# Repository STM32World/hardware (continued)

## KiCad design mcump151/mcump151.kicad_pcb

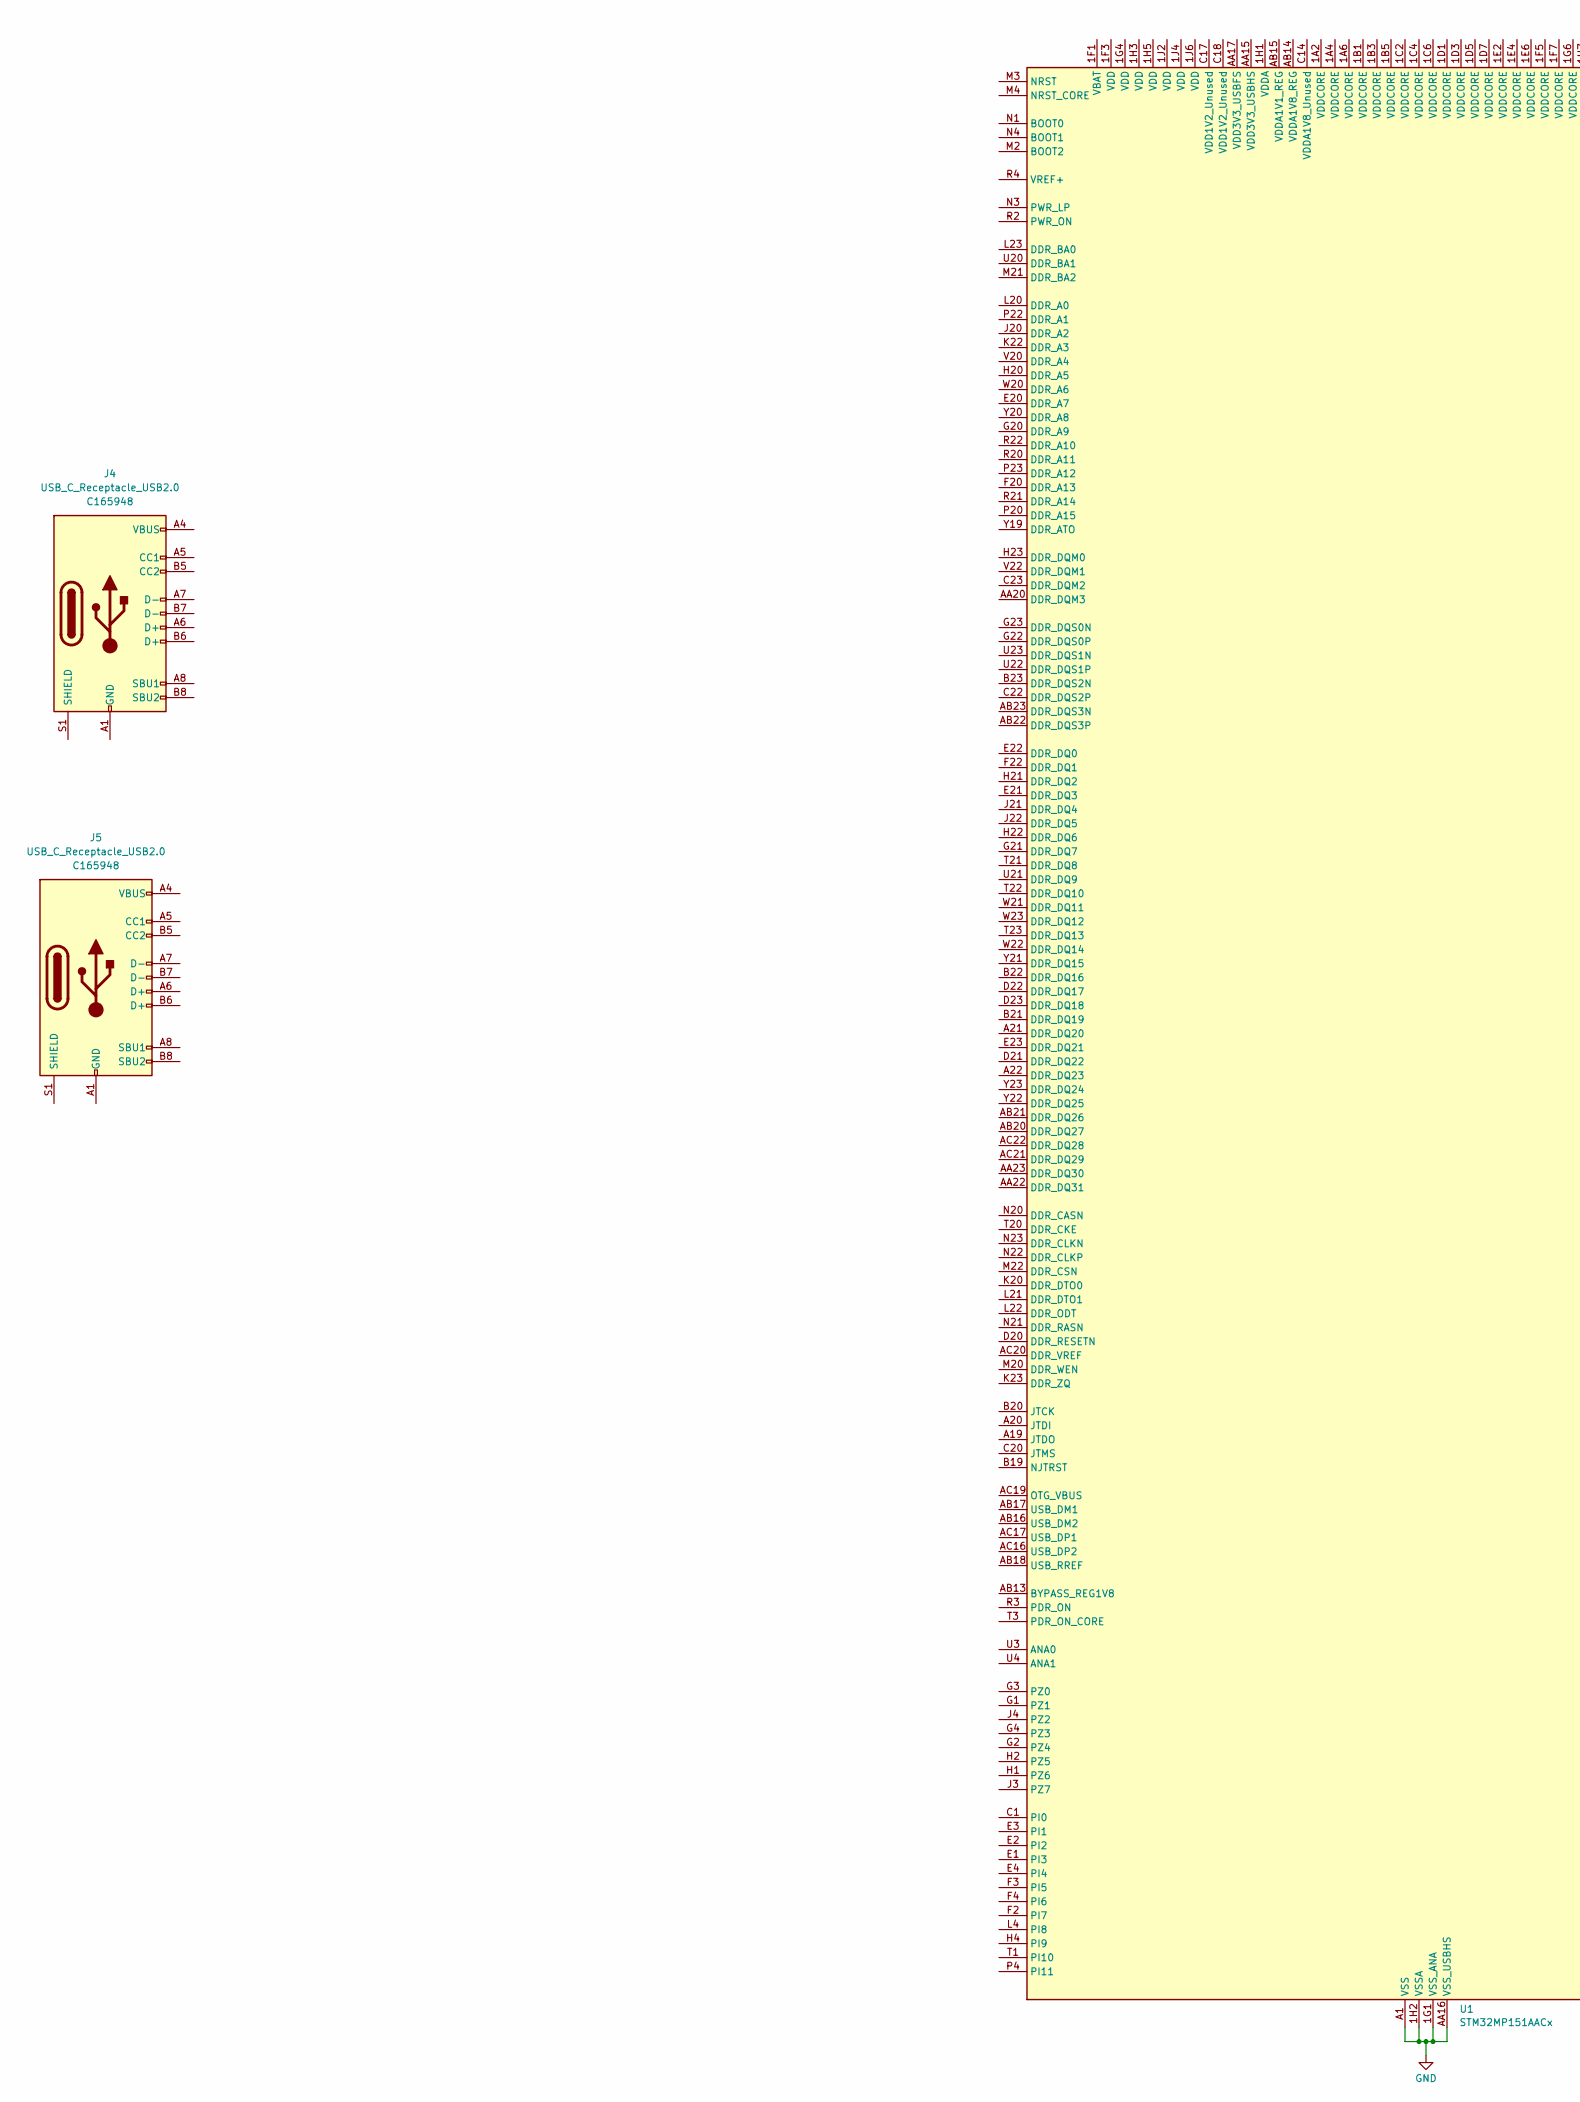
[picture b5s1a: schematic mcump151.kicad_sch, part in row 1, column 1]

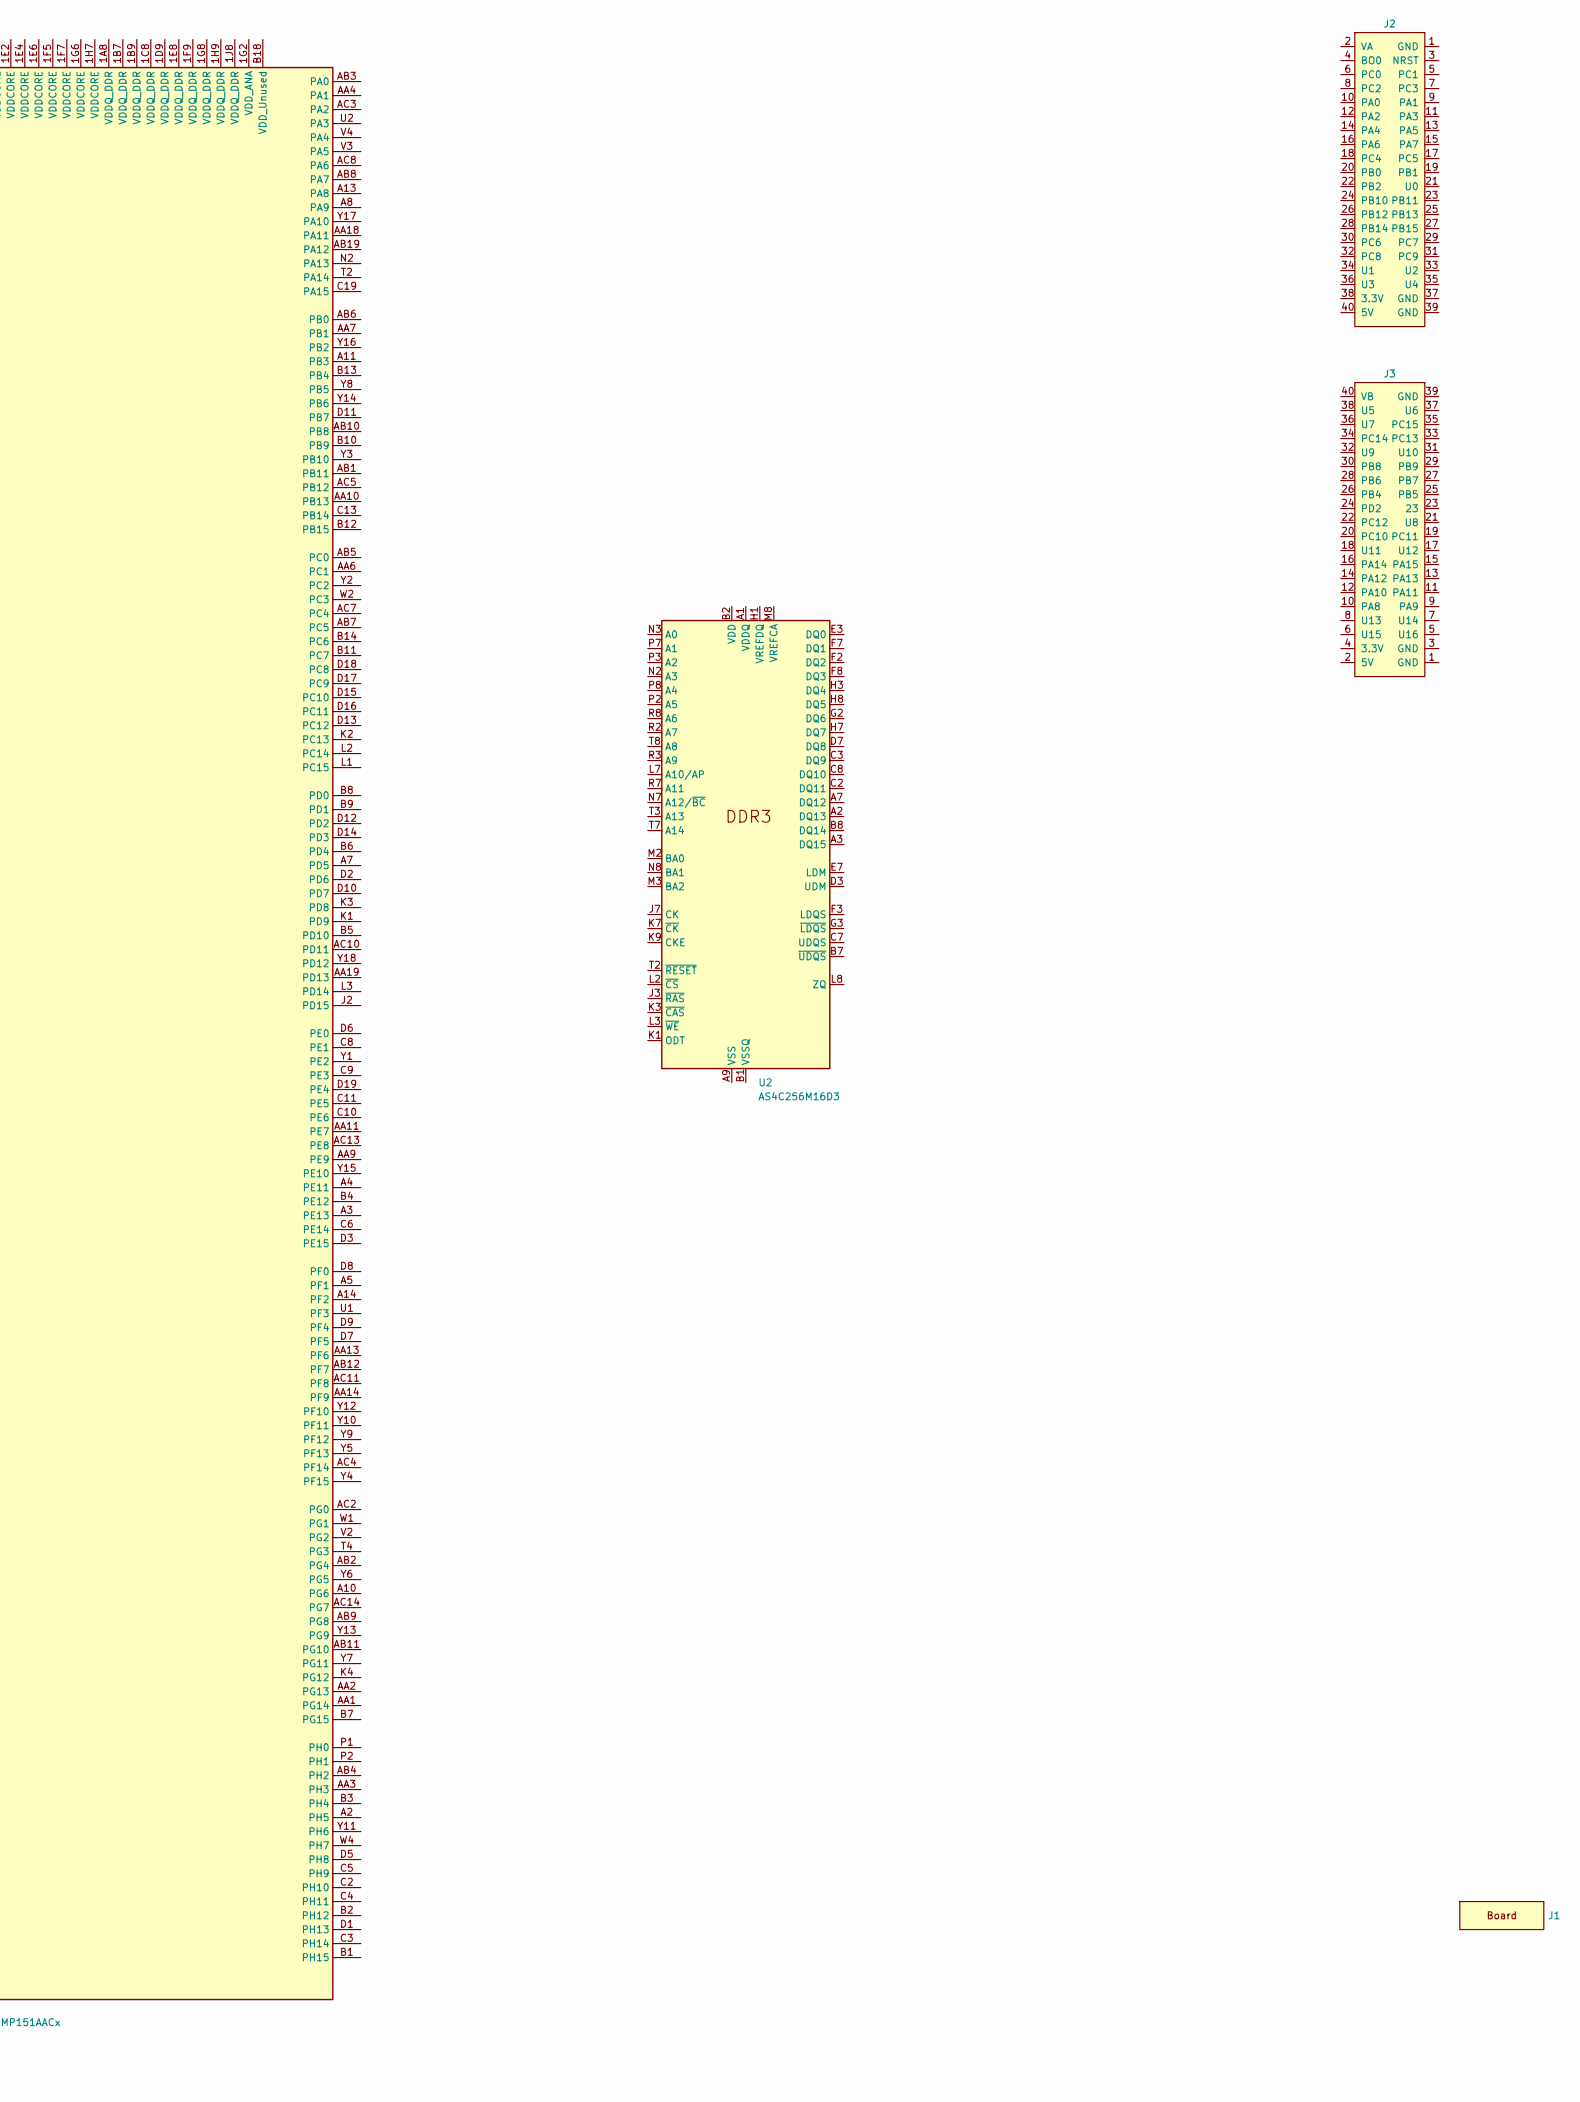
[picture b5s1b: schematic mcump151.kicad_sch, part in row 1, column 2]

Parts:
J1: STM32WORLD_BOARD
J2: STM32WORLD_CONNECTOR_1; PinSocket_2x20_P2.54mm_Vertical_Stackable; LCSC C35165
J3: STM32WORLD_CONNECTOR_2; PinSocket_2x20_P2.54mm_Vertical_Stackable; LCSC C35165
J4, J5: USB_C_Receptacle_USB2.0; USB_C_Receptacle_HRO_TYPE-C-31-M-12; LCSC C165948
U1: STM32MP151AACx; ST_TFBGA-361_12x12mm_Layout23x23_P0.5mmP0.65mm; LCSC C1555473
U2: AS4C256M16D3; BGA-96_9.0x13.0mm_Layout2x3x16_P0.8mm

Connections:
GND: U1.1A3 (VSS), U1.1A5 (VSS), U1.1A7 (VSS), U1.1B2 (VSS), U1.1B4 (VSS), U1.1B6 (VSS), U1.1B8 (VSS), U1.1C1 (VSS), U1.1C3 (VSS), U1.1C5 (VSS), U1.1C7 (VSS), U1.1C9 (VSS), U1.1D2 (VSS), U1.1D4 (VSS), U1.1D6 (VSS), U1.1D8 (VSS), U1.1E1 (VSS), U1.1E3 (VSS), U1.1E5 (VSS), U1.1E7 (VSS), U1.1E9 (VSS), U1.1F2 (VSS), U1.1F4 (VSS), U1.1F6 (VSS), U1.1F8 (VSS), U1.1G1 (VSS_ANA), U1.1G3 (VSS), U1.1G5 (VSS), U1.1G7 (VSS), U1.1G9 (VSS), U1.1H2 (VSSA), U1.1H4 (VSS), U1.1H6 (VSS), U1.1H8 (VSS), U1.1J3 (VSS), U1.1J5 (VSS), U1.1J7 (VSS), U1.A1 (VSS), U1.A23 (VSS), U1.AA5 (VSS), U1.AA8 (VSS), U1.AA12 (VSS), U1.AA16 (VSS_USBHS), U1.AA21 (VSS), U1.AC1 (VSS), U1.AC23 (VSS), U1.C7 (VSS), U1.C12 (VSS), U1.C16 (VSS), U1.C21 (VSS), U1.D4 (VSS), U1.F21 (VSS), U1.H3 (VSS), U1.K21 (VSS), U1.P3 (VSS), U1.P21 (VSS), U1.V21 (VSS), U1.W3 (VSS)
unnamed: J4.A1 (GND), J4.A12 (GND), J4.B1 (GND), J4.B12 (GND)
unnamed: J4.A4 (VBUS), J4.A9 (VBUS), J4.B4 (VBUS), J4.B9 (VBUS)
unnamed: J5.A1 (GND), J5.A12 (GND), J5.B1 (GND), J5.B12 (GND)
unnamed: J5.A4 (VBUS), J5.A9 (VBUS), J5.B4 (VBUS), J5.B9 (VBUS)
unnamed: U2.B2 (VDD), U2.D9 (VDD), U2.G7 (VDD), U2.K2 (VDD), U2.K8 (VDD), U2.N1 (VDD), U2.N9 (VDD), U2.R1 (VDD), U2.R9 (VDD)
unnamed: U2.A1 (VDDQ), U2.A8 (VDDQ), U2.C1 (VDDQ), U2.C9 (VDDQ), U2.D2 (VDDQ), U2.E9 (VDDQ), U2.F1 (VDDQ), U2.H2 (VDDQ), U2.H9 (VDDQ)
unnamed: U2.A9 (VSS), U2.B3 (VSS), U2.E1 (VSS), U2.G8 (VSS), U2.J2 (VSS), U2.J8 (VSS), U2.M1 (VSS), U2.M9 (VSS), U2.P1 (VSS), U2.P9 (VSS), U2.T1 (VSS), U2.T9 (VSS)
unnamed: U2.B1 (VSSQ), U2.B9 (VSSQ), U2.D1 (VSSQ), U2.D8 (VSSQ), U2.E2 (VSSQ), U2.E8 (VSSQ), U2.F9 (VSSQ), U2.G1 (VSSQ), U2.G9 (VSSQ)

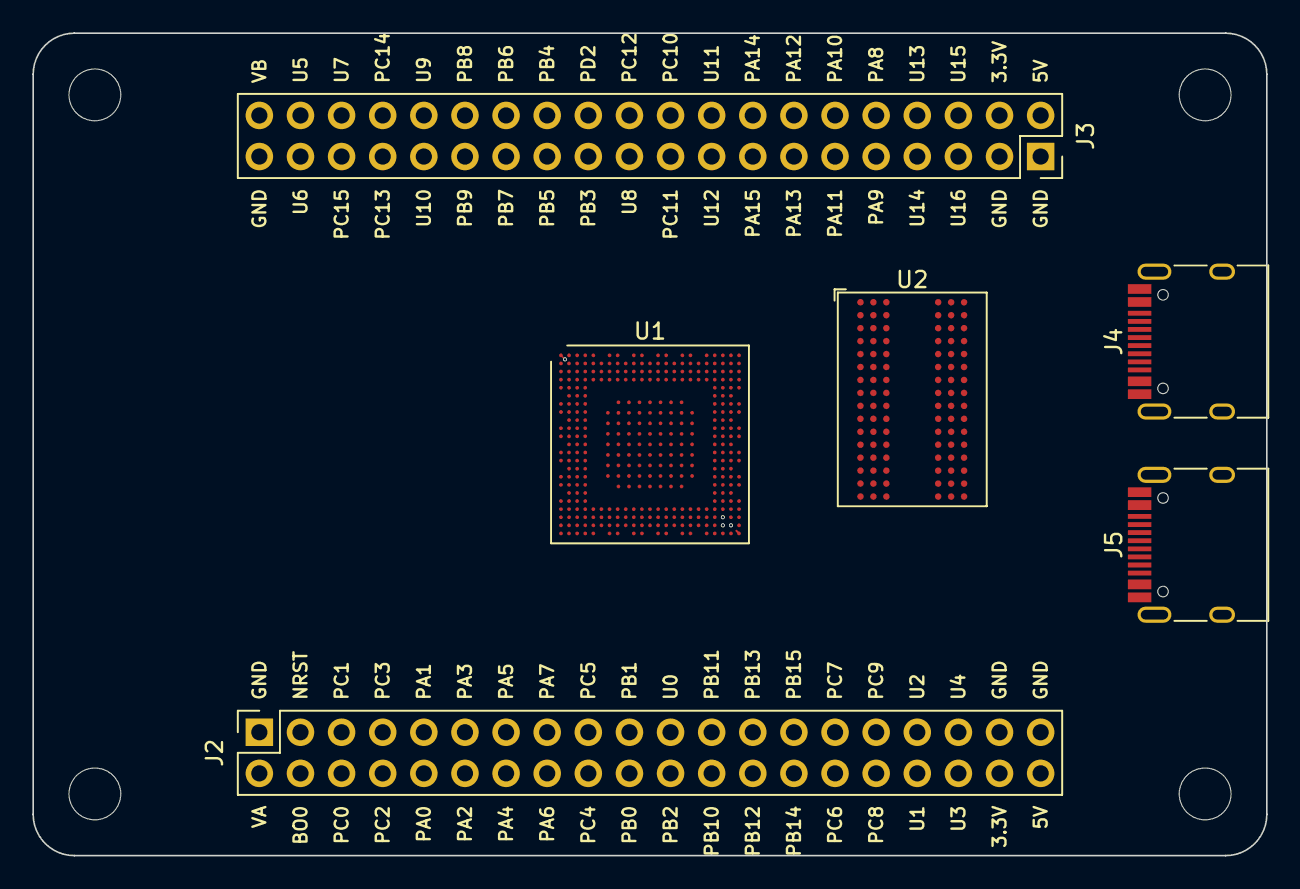
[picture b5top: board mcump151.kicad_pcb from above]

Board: 8 copper layers, 76.2 x 50.8 mm, 7 parts (0 on the bottom side), 9 nets.

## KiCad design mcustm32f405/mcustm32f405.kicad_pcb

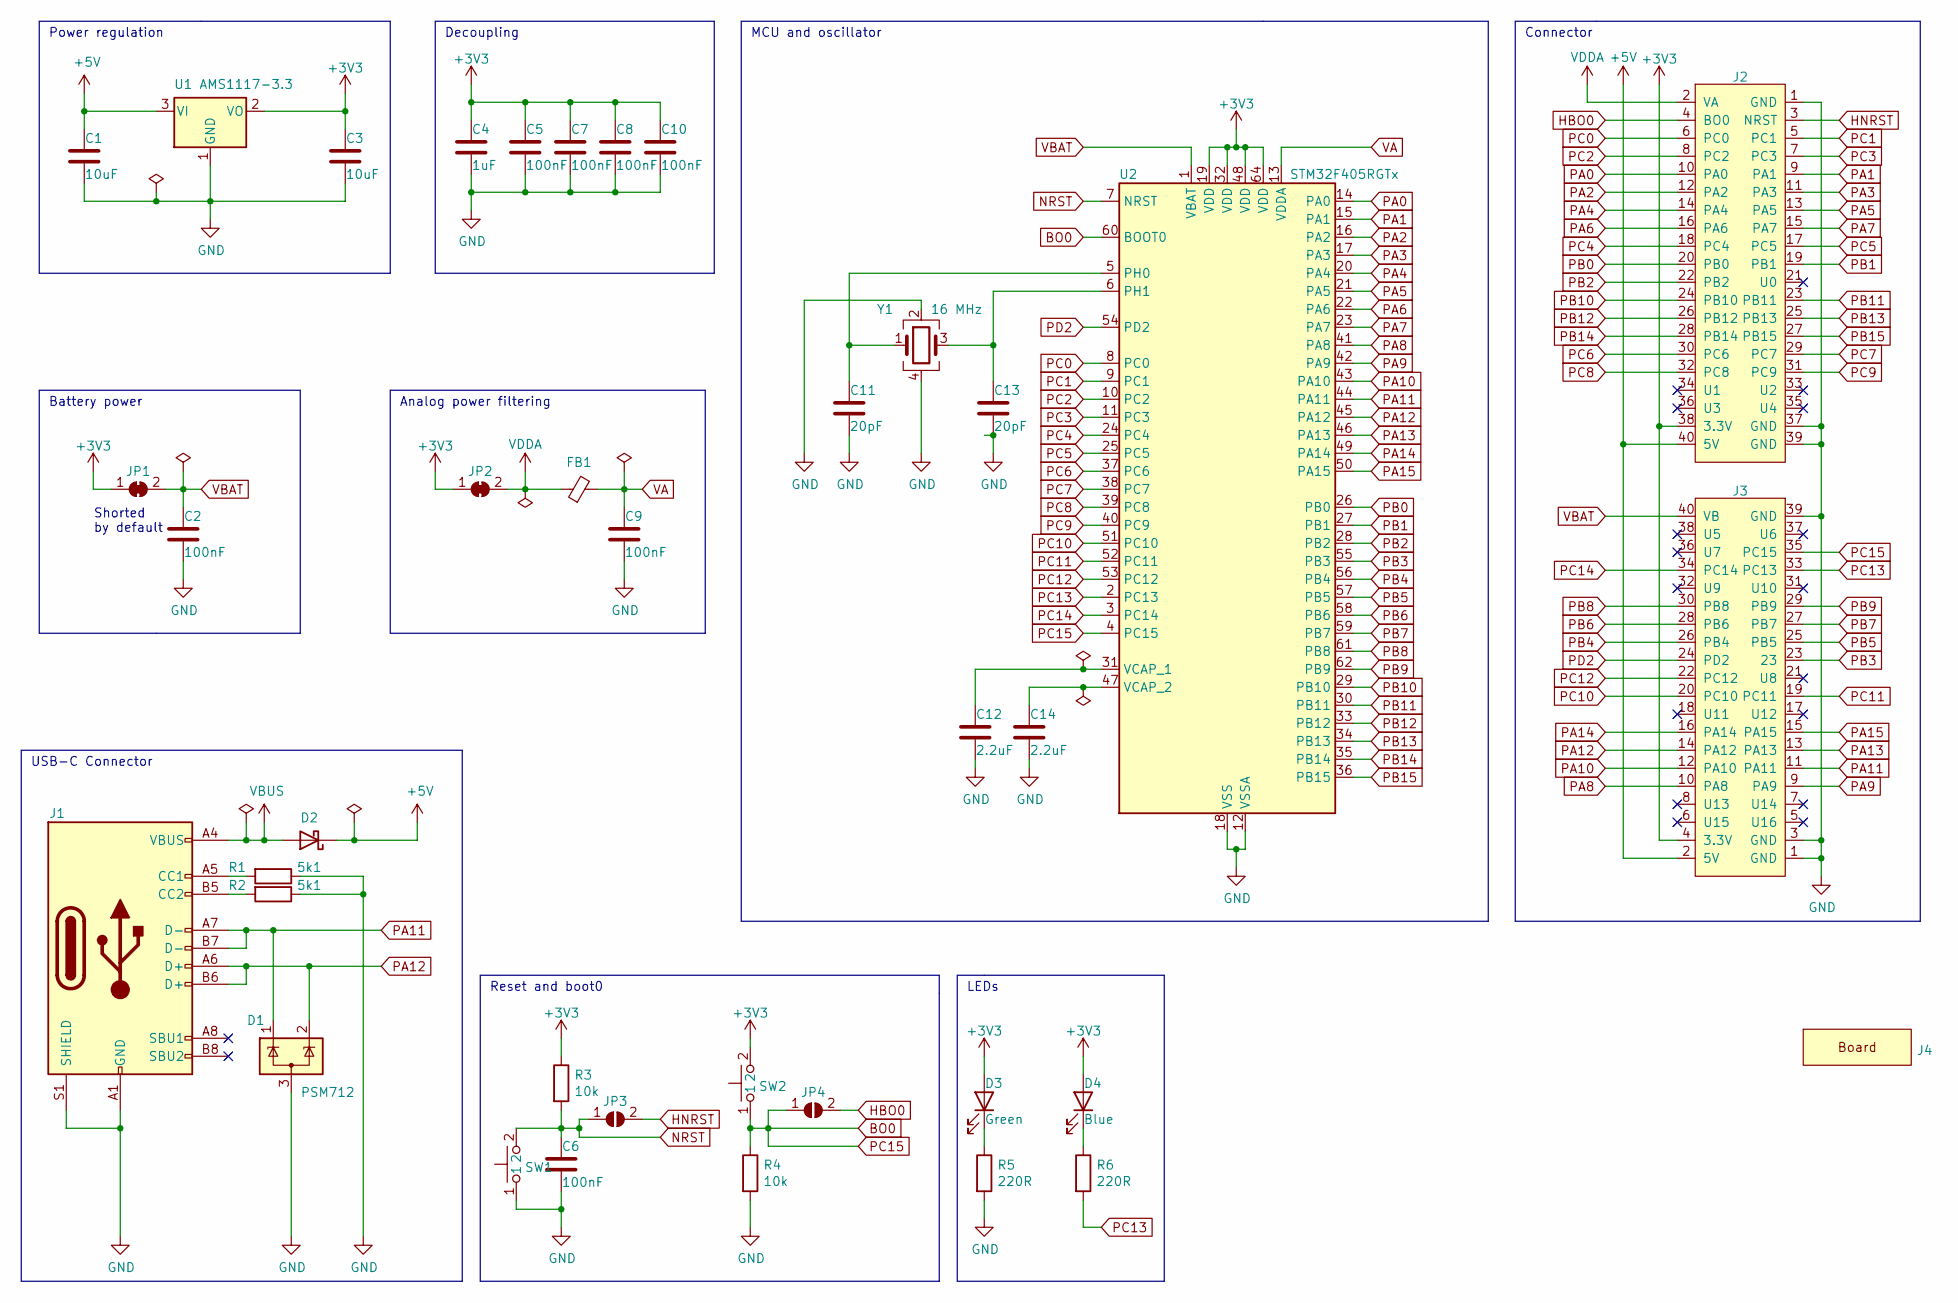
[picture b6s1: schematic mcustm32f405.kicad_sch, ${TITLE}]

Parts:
C1, C3: C_10UF_0805; C_0805_2012Metric; LCSC C15850
C2, C5, C6, C7, C8, C9, C10: C_100NF_0603; C_0603_1608Metric; LCSC C14663
C4: C_1UF_0603; C_0603_1608Metric; LCSC C15849
C11, C13: C_20PF_0603; C_0603_1608Metric; LCSC C1648
C12, C14: C_2.2UF_0603; C_0603_1608Metric; LCSC C23630
D1: PSM712; SOT-23; LCSC C32677
D2: D_SOD-123; LCSC C8598
D3: LED_GREEN_0603; LED_0603_1608Metric; LCSC C72043
D4: LED_BLUE_0603; LED_0603_1608Metric; LCSC C72041
FB1: FB_0603; L_0603_1608Metric; LCSC C1002
J1: USB_C_Receptacle_HRO_TYPE-C-31-M-12; LCSC C165948
J2: STM32WORLD_CONNECTOR_1; PinSocket_2x20_P2.54mm_Vertical_Stackable; LCSC C35165
J3: STM32WORLD_CONNECTOR_2; PinSocket_2x20_P2.54mm_Vertical_Stackable; LCSC C35165
J4: STM32WORLD_BOARD
JP1, JP2: SolderJumper_2_Bridged; SolderJumper-2_P1.3mm_Bridged_RoundedPad1.0x1.5mm
JP3, JP4: SolderJumper-2_P1.3mm_Open_RoundedPad1.0x1.5mm
R1, R2: R_5.1K_0603; R_0603_1608Metric; LCSC C23186
R3, R4: R_10K_0603; R_0603_1608Metric; LCSC C25804
R5, R6: R_220_0603; R_0603_1608Metric; LCSC C22962
SW1, SW2: TS-1088R-02526; LCSC C455281
U1: AMS1117-3.3; SOT-223-3_TabPin2; LCSC C6186
U2: STM32F405RGTx; LQFP-64_10x10mm_P0.5mm; LCSC C15742
Y1: X_16MHZ; Crystal_SMD_3225-4Pin_3.2x2.5mm; LCSC C13738

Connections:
+3V3: C3.1, C4.1, C5.1, C7.1, C8.1, C10.1, D3.2 (A), D4.2 (A), J2.38 (3.3V), J3.4 (3.3V), JP1.1 (A), JP2.1 (A), R3.1, SW2.2, U1.2 (VO), U2.19 (VDD), U2.32 (VDD), U2.48 (VDD), U2.64 (VDD)
+5V: C1.1, D2.1 (K), J2.40 (5V), J3.2 (5V), U1.3 (VI)
BO0: J3.35 (PC15), JP4.1 (A), R4.1, SW2.1, U2.4 (PC15), U2.60 (BOOT0)
GND: C1.2, C2.2, C3.2, C4.2, C5.2, C6.2, C7.2, C8.2, C9.2, C10.2, C11.2, C12.2, C13.2, C14.2, D1.3 (A), J1.A1 (GND), J1.A12 (GND), J1.B1 (GND), J1.B12 (GND), J1.S1 (SHIELD), J2.1 (GND), J2.37 (GND), J2.39 (GND), J3.1 (GND), J3.3 (GND), J3.39 (GND), R1.1, R2.1, R4.2, R5.2, SW1.1, U1.1 (GND), U2.12 (VSSA), U2.18 (VSS), U2.63 (VSS), Y1.2, Y1.4
HBO0: J2.4 (BO0), JP4.2 (B)
HNRST: J2.3 (NRST), JP3.2 (B)
NRST: C6.1, JP3.1 (A), R3.2, SW1.2, U2.7 (NRST)
unnamed: D3.1 (K), R5.1
unnamed: D4.1 (K), R6.1
unnamed: J1.A5 (CC1), R1.2
unnamed: J1.B5 (CC2), R2.2
unnamed: C11.1, U2.5 (PH0), Y1.1
unnamed: C13.1, U2.6 (PH1), Y1.3
unnamed: C12.1, U2.31 (VCAP_1)
unnamed: C14.1, U2.47 (VCAP_2)
PA0: J2.10 (PA0), U2.14 (PA0)
PA1: J2.9 (PA1), U2.15 (PA1)
PA2: J2.12 (PA2), U2.16 (PA2)
PA3: J2.11 (PA3), U2.17 (PA3)
PA4: J2.14 (PA4), U2.20 (PA4)
PA5: J2.13 (PA5), U2.21 (PA5)
PA6: J2.16 (PA6), U2.22 (PA6)
PA7: J2.15 (PA7), U2.23 (PA7)
PA8: J3.10 (PA8), U2.41 (PA8)
PA9: J3.9 (PA9), U2.42 (PA9)
PA10: J3.12 (PA10), U2.43 (PA10)
PA11: D1.1 (K), J1.A7 (D-), J1.B7 (D-), J3.11 (PA11), U2.44 (PA11)
PA12: D1.2 (K), J1.A6 (D+), J1.B6 (D+), J3.14 (PA12), U2.45 (PA12)
PA13: J3.13 (PA13), U2.46 (PA13)
PA14: J3.16 (PA14), U2.49 (PA14)
PA15: J3.15 (PA15), U2.50 (PA15)
PB0: J2.20 (PB0), U2.26 (PB0)
PB1: J2.19 (PB1), U2.27 (PB1)
PB2: J2.22 (PB2), U2.28 (PB2)
PB3: J3.23, U2.55 (PB3)
PB4: J3.26 (PB4), U2.56 (PB4)
PB5: J3.25 (PB5), U2.57 (PB5)
PB6: J3.28 (PB6), U2.58 (PB6)
PB7: J3.27 (PB7), U2.59 (PB7)
PB8: J3.30 (PB8), U2.61 (PB8)
PB9: J3.29 (PB9), U2.62 (PB9)
PB10: J2.24 (PB10), U2.29 (PB10)
PB11: J2.23 (PB11), U2.30 (PB11)
PB12: J2.26 (PB12), U2.33 (PB12)
PB13: J2.25 (PB13), U2.34 (PB13)
PB14: J2.28 (PB14), U2.35 (PB14)
PB15: J2.27 (PB15), U2.36 (PB15)
PC0: J2.6 (PC0), U2.8 (PC0)
PC1: J2.5 (PC1), U2.9 (PC1)
PC2: J2.8 (PC2), U2.10 (PC2)
PC3: J2.7 (PC3), U2.11 (PC3)
PC4: J2.18 (PC4), U2.24 (PC4)
PC5: J2.17 (PC5), U2.25 (PC5)
PC6: J2.30 (PC6), U2.37 (PC6)
PC7: J2.29 (PC7), U2.38 (PC7)
PC8: J2.32 (PC8), U2.39 (PC8)
PC9: J2.31 (PC9), U2.40 (PC9)
PC10: J3.20 (PC10), U2.51 (PC10)
PC11: J3.19 (PC11), U2.52 (PC11)
PC12: J3.22 (PC12), U2.53 (PC12)
PC13: J3.33 (PC13), R6.2, U2.2 (PC13)
PC14: J3.34 (PC14), U2.3 (PC14)
PD2: J3.24 (PD2), U2.54 (PD2)
VA: C9.1, FB1.2, U2.13 (VDDA)
VBAT: C2.1, J3.40 (VB), JP1.2 (B), U2.1 (VBAT)
VBUS: D2.2 (A), J1.A4 (VBUS), J1.A9 (VBUS), J1.B4 (VBUS), J1.B9 (VBUS)
VDDA: FB1.1, J2.2 (VA), JP2.2 (B)

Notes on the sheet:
Connector
Power regulation
Analog power filtering
Shorted by default
Battery power
LEDs
Reset and boot0
USB-C Connector
MCU and oscillator
Decoupling

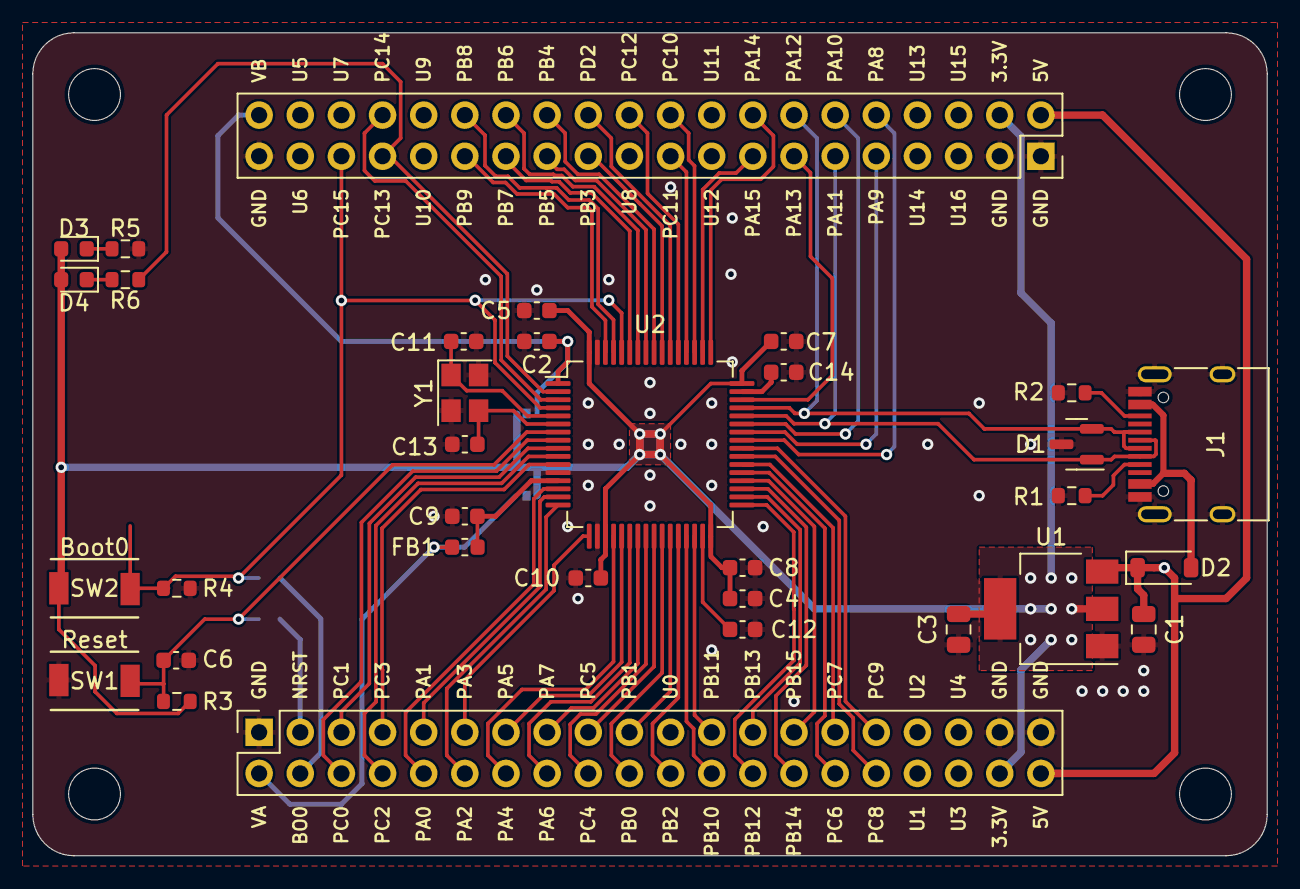
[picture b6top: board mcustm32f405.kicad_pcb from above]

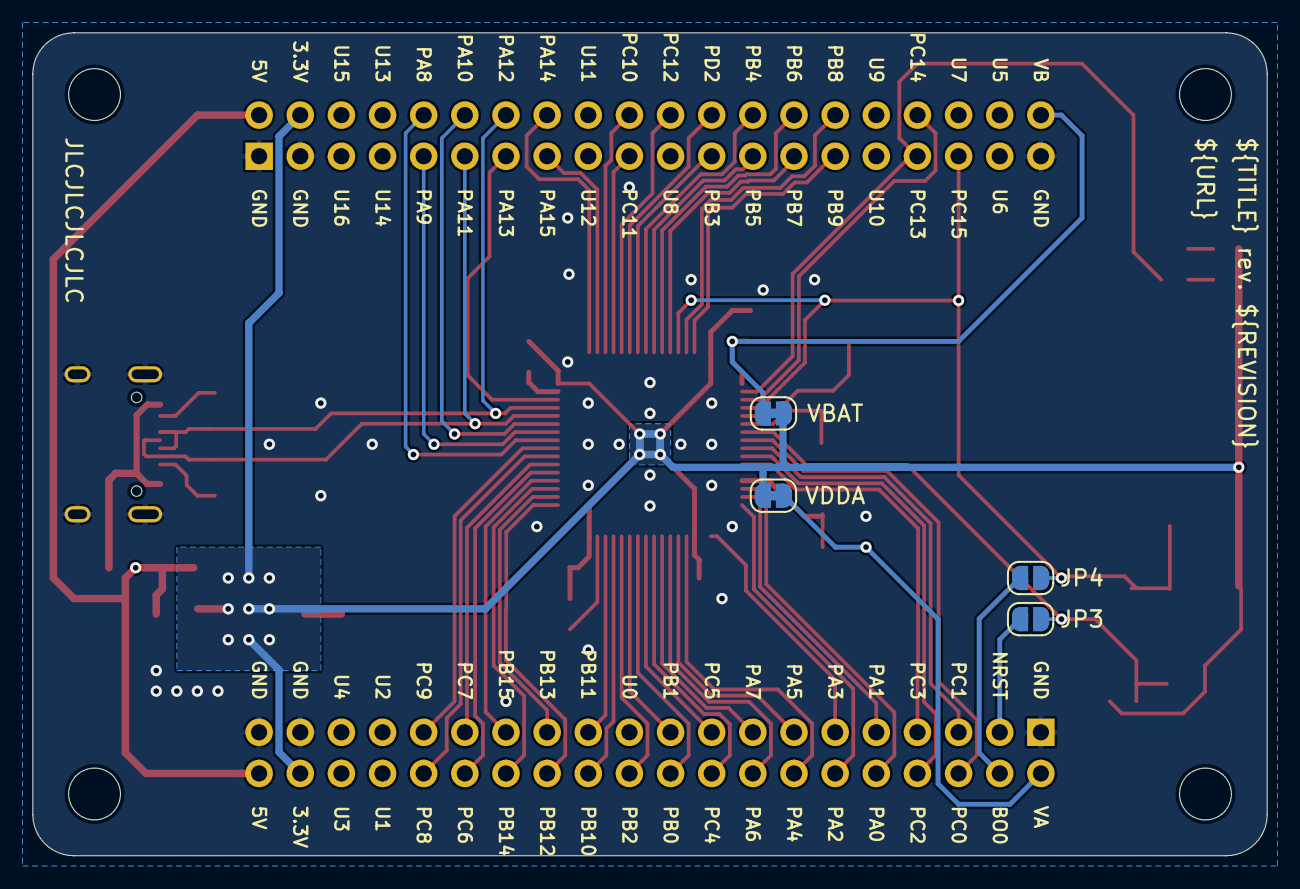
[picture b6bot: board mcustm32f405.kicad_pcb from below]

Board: 2 copper layers, 76.2 x 50.8 mm, 38 parts (4 on the bottom side), 67 nets.
